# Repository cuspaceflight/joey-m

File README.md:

JOEY-M - CU Spaceflight
====================

Joey-M is an experimental flight computer produced as part of the Wombat flight
computer project at Cambridge University Spaceflight.  

It uses a twin varactor crystal pulling arrangement to change the transmit
frequency of a Micrel MICRF112YMM 434MHz ISM band transmitter, along with a dual
DAC from Linear Technology to control the varactor bias voltages.  

The DAC can be any of the LTC range in MSOP-8 package which share a footprint, 
including the LTC1661/1662 (10 bit), LTC2622 (12 bit), LTC2612 (14 bit)
and LTC2602 (16 bit).  

Other equipment on board is a uBlox NEO-6Q GPS, TMP100 12 bit temperature
sensor, and an Atmel ATMEGA328P MCU.  

Designed and released into the public domain by Jon Sowman - March 2012.  

[Contact CUSF](mailto:contact@cusf.co.uk)

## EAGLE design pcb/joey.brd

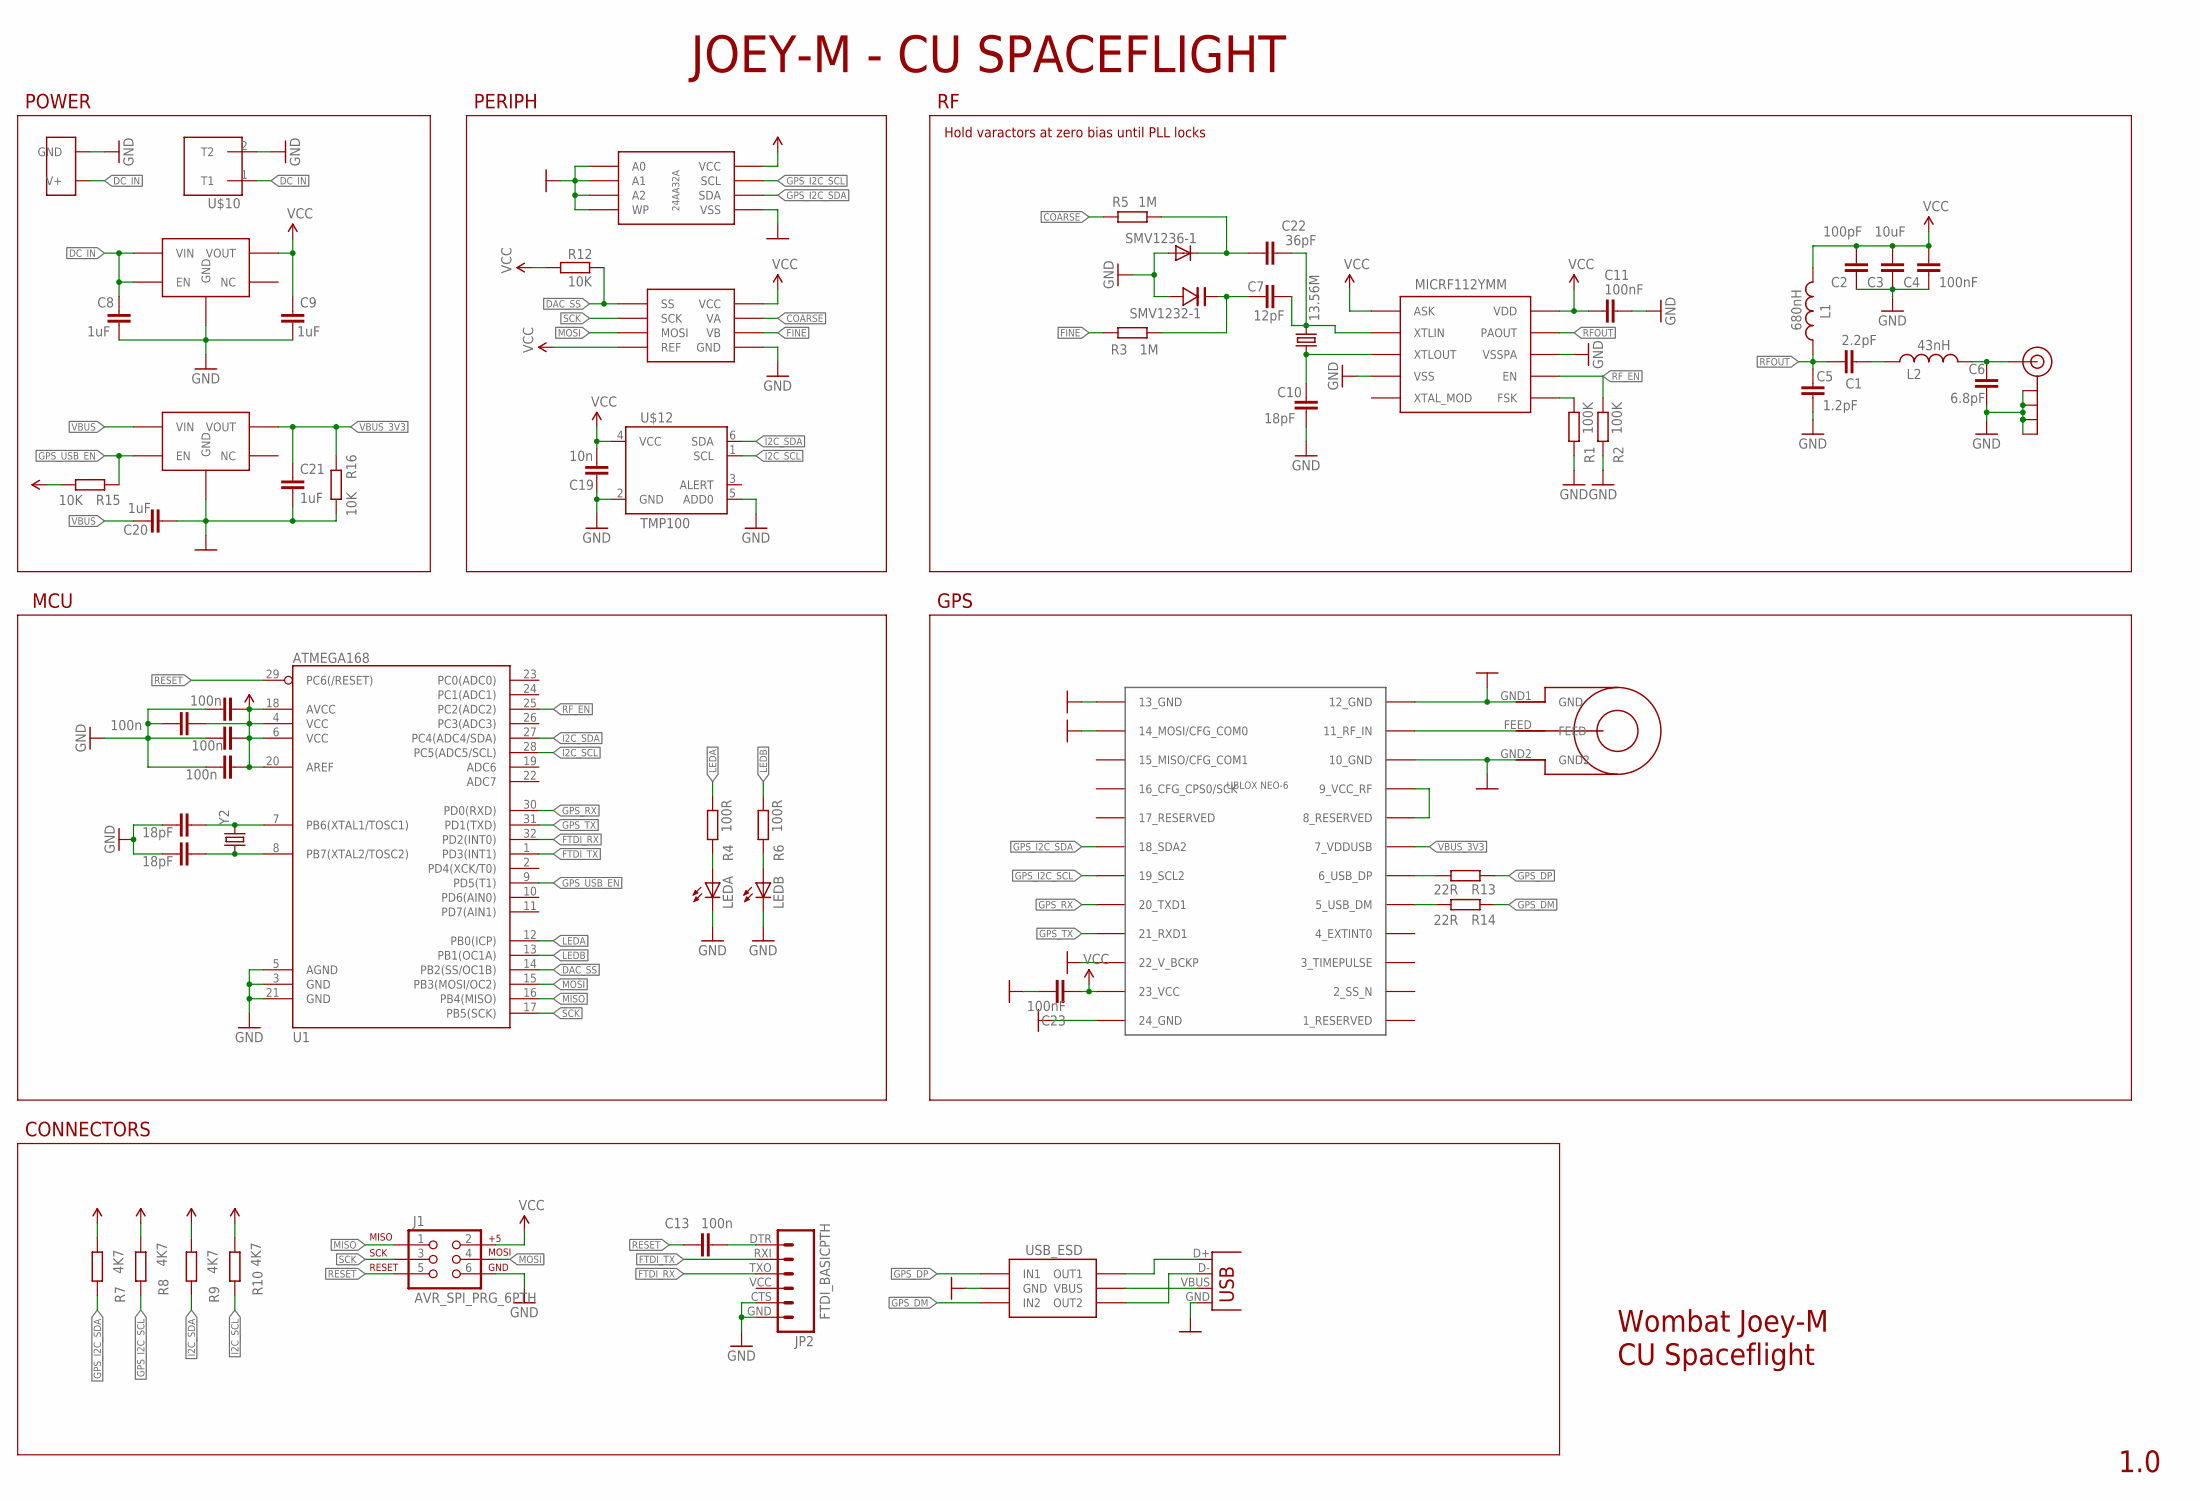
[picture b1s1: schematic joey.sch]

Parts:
C1: 2.2pF; C0603
C2: 100pF; C0603
C3: 10uF; C0603
C4, C11, C23: 100nF; C0603
C5: 1.2pF; C0603
C6: 6.8pF; C0603
C7: 12pF; C0603
C8, C9, C20, C21: 1uF; C0603
C10, C17, C18: 18pF; C0603
C12, C13, C14, C15, C16: 100n; C0603
C19: 10n; C0603
C22: 36pF; C0603
J1: AVR_SPI_PRG_6PTH; 2X3
JP2: FTDI_BASICPTH; FTDI_BASIC
L1: 680nH; 0603
L2: 43nH; C0402
LEDA: LED0603; LED-0603
LEDB: LED0603; LED-0603
R1, R2: 100K; R0603
R3, R5: 1M; R0603
R4, R6: 100R; R0603
R7, R8, R9, R10: 4K7; R0603
R12, R15, R16: 10K; R0603
R13, R14: 22R; R0603
SMV1232-1: SMV1247-VARACTOR; SMV1247-VARACTOR-SC-79
SMV1236-1: DIODESOD; SOD-323
U1: ATMEGA168; TQFP32-08
U$1: MICRF112; MICRF112-MSOP10
U$2: SARANTEL-SR1202
U$3: UBLOX_NEO-6; UBLOX_NEO-6P
U$4, U$9: ADP122AUJZ-3V3REG-5TSOT; SOT23-5L
U$5: JST_SMTSIDE; JST_CONN_SMD
U$6: I2C_EEPROM_24AA32A; MSOP8
U$7: SMA_END_19-70-TGG
U$8: LTC2602_16BIT_DUALDAC; MSOP8
U$10: TE_CONN_TERMBLK; 10A_TECONN_TERMBLK
U$12: TMP100; SOT23-6
USB_ESD: USB_ESD_PROT_USBLC6; SOT23-6
X1: USB-MICROB
Y1: 13.56M; CRYSTAL-SMD-5X3
Y2: CRYSTAL5X3; CRYSTAL-SMD-5X3

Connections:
COARSE: R5.1, U$8.8 (VA)
COARSE_V: C22.1, R5.2, SMV1236-1.1 (C)
DAC_SS: R12.2, U1.14 (PB2(SS/OC1B)), U$8.1 (SS)
DC_IN: C8.2, U$4.1 (VIN), U$4.3 (EN), U$5.VBATT (V+), U$10.1 (T1)
FINE: R3.2, U$8.5 (VB)
FTDI_RX: JP2.TXO (3), U1.32 (PD2(INT0))
FTDI_TX: JP2.RXI (2), U1.1 (PD3(INT1))
GND: C2.1, C3.1, C4.1, C5.1, C6.1, C8.1, C9.1, C10.1, C11.1, C12.2, C14.1, C15.1, C16.1, C17.2, C18.2, C19.1, C20.1, C21.1, C23.1, J1.6, JP2.CTS (5), JP2.GND (6), LEDA.C, LEDB.C, R1.1, R2.1, R16.2, SMV1232-1.AN (ANODE), SMV1236-1.2 (A), U1.3 (GND), U1.5 (AGND), U1.21 (GND), U$1.VSS, U$1.VSSPA, U$2.GND1 (GND), U$2.GND2, U$3.10_GND, U$3.12_GND, U$3.13_GND, U$3.14_MOSI/CFG_COM0, U$3.22_V_BCKP, U$3.24_GND, U$4.2 (GND), U$5.GND, U$6.1 (A0), U$6.2 (A1), U$6.3 (A2), U$6.4 (VSS), U$6.7 (WP), U$7.GND1 (GND), U$7.GND2 (GND), U$7.GND3 (GND), U$7.GND4 (GND), U$8.7 (GND), U$9.2 (GND), U$10.2 (T2), U$12.2 (GND), U$12.5 (ADD0), USB_ESD.2 (GND), X1.GND
GPS_DM: R14.1, USB_ESD.3 (IN2)
GPS_DP: R13.1, USB_ESD.1 (IN1)
GPS_I2C_SCL: R8.1, U$3.19_SCL2, U$6.6 (SCL)
GPS_I2C_SDA: R7.1, U$3.18_SDA2, U$6.5 (SDA)
GPS_RX: U1.30 (PD0(RXD)), U$3.20_TXD1
GPS_TX: U1.31 (PD1(TXD)), U$3.21_RXD1
GPS_USB_EN: R15.1, U1.9 (PD5(T1)), U$9.3 (EN)
I2C_SCL: R10.1, U1.28 (PC5(ADC5/SCL)), U$12.1 (SCL)
I2C_SDA: R9.1, U1.27 (PC4(ADC4/SDA)), U$12.6 (SDA)
LEDA: R4.2, U1.12 (PB0(ICP))
LEDB: R6.2, U1.13 (PB1(OC1A))
MISO: J1.1, U1.16 (PB4(MISO))
MOSI: J1.4, U1.15 (PB3(MOSI/OC2)), U$8.3 (MOSI)
unnamed: R1.2, U$1.FSK
unnamed: C10.2, U$1.XTLOUT, Y1.1
unnamed: C13.2, JP2.DTR (1)
unnamed: C7.2, C22.2, U$1.XTLIN, Y1.3 (2)
unnamed: C1.2, L2.1
unnamed: C6.2, L2.2, U$7.RF (SIGNAL)
unnamed: C7.1, R3.1, SMV1232-1.CAT (CATHODE)
unnamed: LEDA.A, R4.1
unnamed: C17.1, U1.7 (PB6(XTAL1/TOSC1)), Y2.3 (2)
unnamed: C18.1, U1.8 (PB7(XTAL2/TOSC2)), Y2.1
unnamed: U$2.FEED, U$3.11_RF_IN
unnamed: LEDB.A, R6.1
unnamed: U$3.8_RESERVED, U$3.9_VCC_RF
unnamed: USB_ESD.4 (OUT2), X1.D-
unnamed: USB_ESD.6 (OUT1), X1.D+
unnamed: R13.2, U$3.6_USB_DP
unnamed: R14.2, U$3.5_USB_DM
RESET: C13.1, J1.5, U1.29 (PC6(/RESET))
RFOUT: C1.1, C5.2, L1.1, U$1.PAOUT
RF_EN: R2.2, U1.25 (PC2(ADC2)), U$1.EN
SCK: J1.3, U1.17 (PB5(SCK)), U$8.2 (SCK)
VBUS: C20.2, U$9.1 (VIN), USB_ESD.5 (VBUS), X1.VBUS
VBUS_3V3: C21.2, R16.1, U$3.7_VDDUSB, U$9.5 (VOUT)
VCC: C2.2, C3.2, C4.2, C9.2, C11.2, C12.1, C14.2, C15.2, C16.2, C19.2, C23.2, J1.2, L1.2, R7.2, R8.2, R9.2, R10.2, R12.1, R15.2, U1.4 (VCC), U1.6 (VCC), U1.18 (AVCC), U1.20 (AREF), U$1.ASK, U$1.VDD, U$3.23_VCC, U$4.5 (VOUT), U$6.8 (VCC), U$8.4 (REF), U$8.6 (VCC), U$12.4 (VCC)

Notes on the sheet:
Wombat Joey-M
CU Spaceflight
1.0
Hold varactors at zero bias until PLL locks
JOEY-M - CU SPACEFLIGHT
POWER
MCU
GPS
PERIPH
CONNECTORS

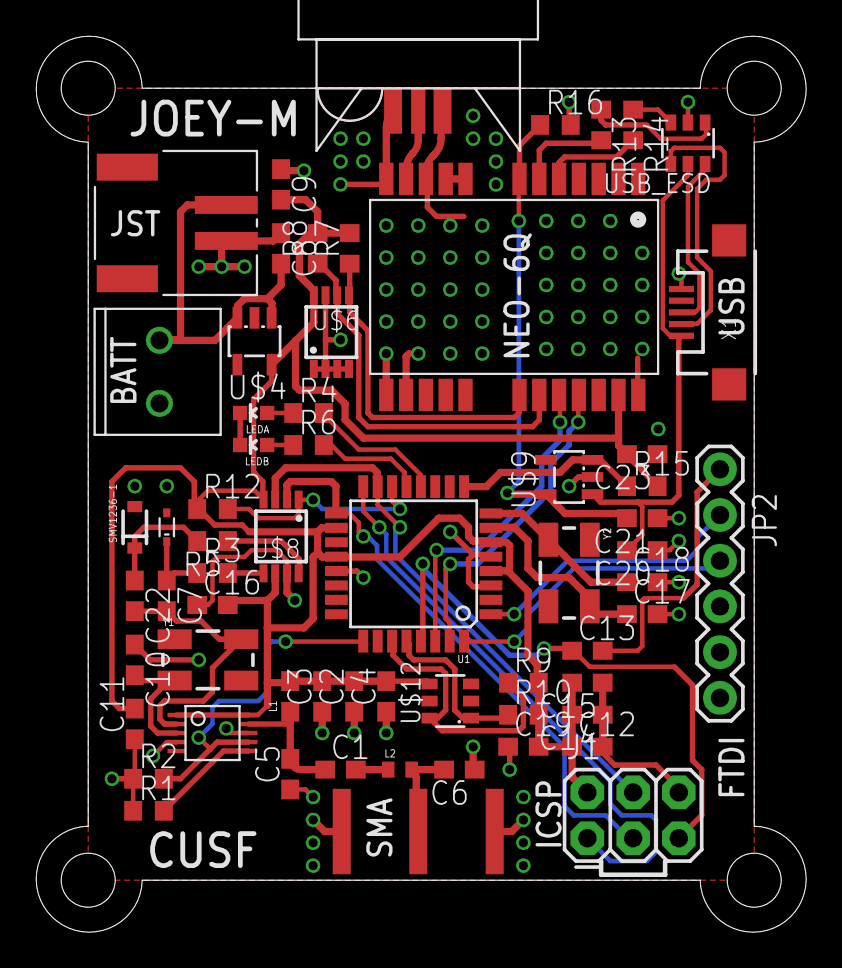
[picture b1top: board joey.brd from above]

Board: 2 copper layers, 42.7 x 49.7 mm, 63 parts (1 on the bottom side), 45 nets.

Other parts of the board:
U$11: CUSF_LOGO_LARGE

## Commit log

2011-10-03 Initial
2011-10-07 Added values to caps and added the varactor datasheet
2012-03-07 First commit of joey-m
2012-03-07 Added remaining board files
2012-03-08 Fixed filter bug in the schematic, almost finished routing
2012-03-08 Finished routing for v1.0
2012-03-10 Finished routing, updated completed BOM for v1.0
2012-03-10 Fixed green LED part no
2012-03-11 Added some final silk and generated gerbers for 1.0
2012-03-15 Changed to a different 18PF cap since the other was out of stock
2012-03-15 Adding readme
2012-03-15 Ooops, README in the right place
2012-03-15 PNGs of schematic and board
2012-03-17 Started work on firmware
2012-03-18 Git Ignore
2012-03-18 Working DAC code and radio is transmitting
2012-03-18 Moved firmware to its own dir
2012-03-18 Fixed the varactor grounding bug in v1.0
2012-03-18 Started work on interrupt driven radio code
2012-03-18 Working 50 baud RTTY
2012-03-19 Investigating sidebands
2012-03-19 upped the DAC SPI interface speed to 8M
2012-03-19 First try at a Blackman order 8 FIR
2012-03-19 optimising the DAC write routine
2012-03-20 Working order 50 ramp response
2012-03-20 Working order 50 transitioning, using a ramp response atm http://imgur.com/UC2V2
2012-03-20 Interrupt driven RTTY decoding proeprly
2012-03-20 Switch to a Gaussian filter window
2012-03-20 Made flashing EEPROM a seperate target in Makefile
2012-03-20 Started work on GPS parsing. Successfully polling for a POSLLH message and verifying the sync and ID fields of the returned packet
2012-03-21 Added a function to monitor for GPS lock
2012-03-22 Working POSLLH parsing code from GPS, added filter eep binary
2012-03-22 Added gps_get_time() and _gps_send_msg(), and cleaned up code a bit
2012-03-22 Added gps_num_sats() to get the current number of sats the GPS is tracking
2012-03-22 Fixed an array declaration
2012-03-23 Fixed things for a 2 byte length field, working lat, long, alt, time, no of sats and lock quality
2012-03-23 Added a wrapper UBX checksum parsing function and we now check all GPS transactions for correct checksums
2012-03-23 Did a Bad Thing and linked against the full version of vfprintf for floating point support
2012-03-23 Added checksumming to radio sentences
2012-03-23 Started work on TMP102 code but it's not working yet
2012-03-23 Actually added the temperature stuff...
2012-03-25 Hold last known good data
2012-03-26 Fixed number of sats and tidied up the GPS code a bit. still working on temp sensor
2012-03-26 System ticks counter is now stored in eeprom
2012-03-26 Enabled the watchdog timer
2012-03-26 Moved global defs to invididual files, dunno why I didn't do that from the start really
2012-03-26 Added watchdog timer resetting after each byte transmitted over radio as otherwise 50 baud causes it to to time out, aah
2012-03-26 Checked for correct nav mode - airborne <1g, but doesn't actually do anything if it's wrong
2012-03-27 Added some radio chatter to make Joey easier to find when powering up and to identify by ear during telemetry transmissions
2012-03-29 Changed crystal hardware, adjusted code to run at 434000kHz
2012-03-29 Added telem log and raw sentence parser from nova 21
2012-03-29 Moved gerbers to pcb/
2012-04-02 python script to make a KML file, required simplekml
2012-04-23 Martlet version
2012-08-08 New crystal, updated some defines to match and correct the shift
2012-10-04 Started doing r2
2012-10-04 Finished rev2 of Joey, submission to CCC at this SHA1
2012-10-10 Added batt holder to bom
2012-10-21 Switched the 10UF cap for one that farnell still stocks
2012-10-26 Removed the temperature stuff since I want to start it from scratch
2012-10-26 Updated README with new DAC options
2012-10-26 Added some comments to the LED files
2012-11-02 Empty files for the temperature stuff
2012-11-09 temp stuff
2012-11-09 Continued working on temp sensor stuff. Need to decide to to determine the end of transmission from the slave
2012-11-16 in theory a complete tmp100 interrupt driven implementation. it compiles, therefore it works. right. right?
2012-11-16 Integrating the tmp100 code into the main stuff but it's not actually working yet
2012-11-23 Fixed a typo causing the temp interrupt system to break completely
2012-11-23 ok, the temp read stuff completes fine but unsure if it actually works. need to check the read section
2012-11-23 Just tidying some bits for testing the temp sensor, disabled all other functionality for now
2012-12-13 Working temp sensor though the values are a tad weird
2012-12-14 Working firmware
2014-08-12 re-enable the watchdog timer
2015-04-19 temperature sensor is broken below -19C
2015-04-19 set callsign in Makefile
2015-04-19 ignore main.eep
2015-04-19 set radio centre freq in makefile
2015-09-19 fix compiler warnings (one was an actual bug!)
